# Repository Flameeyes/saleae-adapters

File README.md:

<!--
SPDX-FileCopyrightText: 2021 Diego Elio Pettenò

SPDX-License-Identifier: 0BSD
-->

# Saleae Adapters by Flameeyes

This repository contains a number of [Saleae Logic](https://www.saleae.com/) adapter boards, which
I (Flameeyes) designed for my own use, and decided to share with everyone else.

Note that I have no connection or partnernship with Saleae, so these boards are not officially
supported by them, and honestly not even by me.
I'll be happy to answer questions, but there's no implied support for mistakes or issues caused by
these devices.

## `trrs-mitm`

This is a simple adapter that plugs directly into the Logic (tested with Logic Pro 16, should work
with all models) and provides two TRRS (Tip-Ring-Ring-Sleeve) plugs, plus four breakout pins.

Note: all the components are through-hole for this particular board.

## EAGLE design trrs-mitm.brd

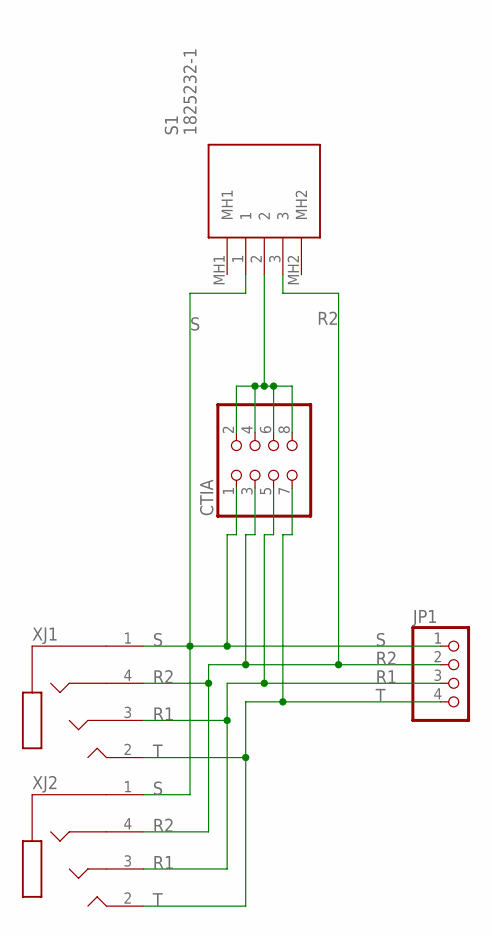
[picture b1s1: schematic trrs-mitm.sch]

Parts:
CTIA: PINHD-2X4/90; 2X04/90
JP1: PINHD-1X4; 1X04
S1: 1825232-1; 18252321
XJ1, XJ2: ASJ171B

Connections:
unnamed: CTIA.2, CTIA.4, CTIA.6, CTIA.8, S1.2
R1: CTIA.5, JP1.3, XJ1.3, XJ2.3
R2: CTIA.3, JP1.2, S1.3, XJ1.4, XJ2.4
S: CTIA.1, JP1.1, S1.1, XJ1.1, XJ2.1
T: CTIA.7, JP1.4, XJ1.2, XJ2.2

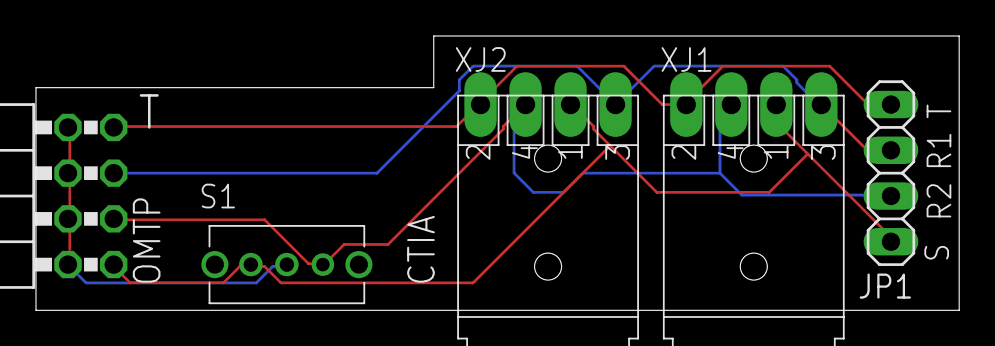
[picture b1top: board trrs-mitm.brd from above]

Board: 2 copper layers, 51.3 x 15.2 mm, 5 parts (0 on the bottom side), 5 nets.

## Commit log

2021-06-11 Remove text normalization.
2021-06-11 Initial import of trrs-mitm.
    This includes documentation and licensing of course.

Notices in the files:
trrs-mitm.brd:
Copyright © 2020 D.E. Pettenò
Licensed under 0BSD License
